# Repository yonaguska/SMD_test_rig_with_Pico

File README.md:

# SMD_test_rig_with_Pico
This is an automated test system for the SMD watchdog timers.

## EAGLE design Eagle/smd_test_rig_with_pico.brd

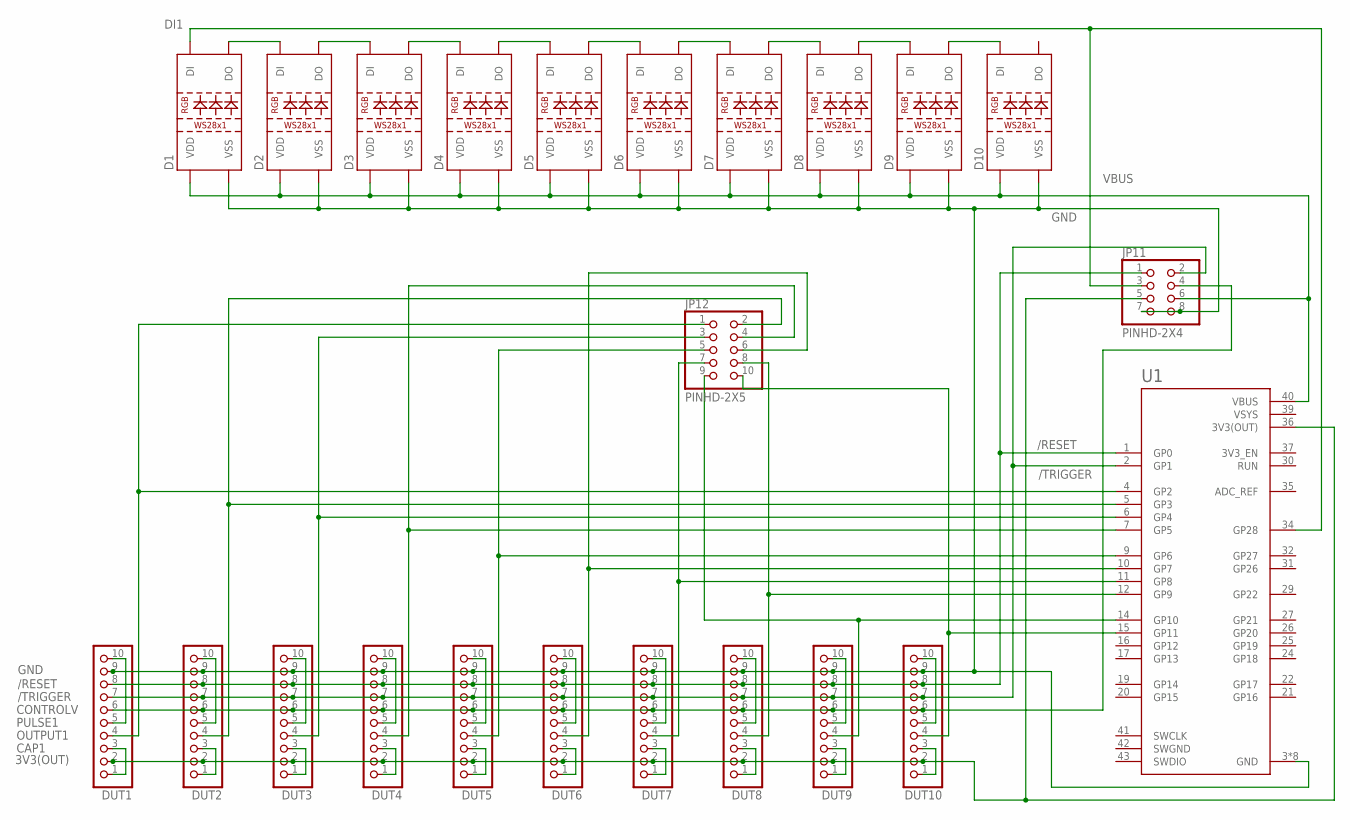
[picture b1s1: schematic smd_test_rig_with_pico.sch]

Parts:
D1, D2, D3, D4, D5, D6, D7, D8, D9, D10: WS2812B
DUT1, DUT2, DUT3, DUT4, DUT5, DUT6, DUT7, DUT8, DUT9, DUT10: PINHD-1X10; 1X10
JP11: PINHD-2X4; 2X04
JP12: PINHD-2X5; 2X05
U1: RASPBERRY_PICO; PICO-PKG-TH

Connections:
3V3(OUT): DUT1.2, DUT2.2, DUT3.2, DUT4.2, DUT5.2, DUT6.2, DUT7.2, DUT8.2, DUT9.2, DUT10.2, JP11.5, U1.36 (3V3(OUT))
/RESET: DUT1.8, DUT2.8, DUT3.8, DUT4.8, DUT5.8, DUT6.8, DUT7.8, DUT8.8, DUT9.8, DUT10.8, JP11.1, U1.1 (GP0)
/TRIGGER: DUT1.7, DUT2.7, DUT3.7, DUT4.7, DUT5.7, DUT6.7, DUT7.7, DUT8.7, DUT9.7, DUT10.7, JP11.2, U1.2 (GP1)
CAP1: DUT1.1, DUT1.3
CAP2: DUT2.1, DUT2.3
CAP3: DUT3.1, DUT3.3
CAP4: DUT4.1, DUT4.3
CAP5: DUT5.1, DUT5.3
CAP6: DUT6.1, DUT6.3
CAP7: DUT7.1, DUT7.3
CAP8: DUT8.1, DUT8.3
CAP9: DUT9.1, DUT9.3
CAP10: DUT10.1, DUT10.3
CONTROLV: DUT1.6, DUT2.6, DUT3.6, DUT4.6, DUT5.6, DUT6.6, DUT7.6, DUT8.6, DUT9.6, DUT10.6, JP11.4
DI1: D1.4 (DI), JP11.3, U1.34 (GP28)
GND: D1.3 (VSS), D2.3 (VSS), D3.3 (VSS), D4.3 (VSS), D5.3 (VSS), D6.3 (VSS), D7.3 (VSS), D8.3 (VSS), D9.3 (VSS), D10.3 (VSS), DUT1.9, DUT2.9, DUT3.9, DUT4.9, DUT5.9, DUT6.9, DUT7.9, DUT8.9, DUT9.9, DUT10.9, JP11.7, JP11.8, U1.3 (GND), U1.8 (GND), U1.13 (GND), U1.18 (GND), U1.23 (GND), U1.28 (GND), U1.33 (GND), U1.38 (GND)
unnamed: D1.2 (DO), D2.4 (DI)
unnamed: D2.2 (DO), D3.4 (DI)
unnamed: D3.2 (DO), D4.4 (DI)
unnamed: D4.2 (DO), D5.4 (DI)
unnamed: D5.2 (DO), D6.4 (DI)
unnamed: D6.2 (DO), D7.4 (DI)
unnamed: D7.2 (DO), D8.4 (DI)
unnamed: D8.2 (DO), D9.4 (DI)
unnamed: D9.2 (DO), D10.4 (DI)
OUTPUT1: DUT1.4, JP12.1, U1.4 (GP2)
OUTPUT2: DUT2.4, JP12.2, U1.5 (GP3)
OUTPUT3: DUT3.4, JP12.3, U1.6 (GP4)
OUTPUT4: DUT4.4, JP12.4, U1.7 (GP5)
OUTPUT5: DUT5.4, JP12.5, U1.9 (GP6)
OUTPUT6: DUT6.4, JP12.6, U1.10 (GP7)
OUTPUT7: DUT7.4, JP12.7, U1.11 (GP8)
OUTPUT8: DUT8.4, JP12.8, U1.12 (GP9)
OUTPUT9: DUT9.4, JP12.9, U1.14 (GP10)
OUTPUT10: DUT10.4, JP12.10, U1.15 (GP11)
PULSE1: DUT1.5, DUT1.10
PULSE2: DUT2.5, DUT2.10
PULSE3: DUT3.5, DUT3.10
PULSE4: DUT4.5, DUT4.10
PULSE5: DUT5.5, DUT5.10
PULSE6: DUT6.5, DUT6.10
PULSE7: DUT7.5, DUT7.10
PULSE8: DUT8.5, DUT8.10
PULSE9: DUT9.5, DUT9.10
PULSE10: DUT10.5, DUT10.10
SWGND: U1.42 (SWGND)
VBUS: D1.1 (VDD), D2.1 (VDD), D3.1 (VDD), D4.1 (VDD), D5.1 (VDD), D6.1 (VDD), D7.1 (VDD), D8.1 (VDD), D9.1 (VDD), D10.1 (VDD), JP11.6, U1.40 (VBUS)
VSYS: U1.39 (VSYS)

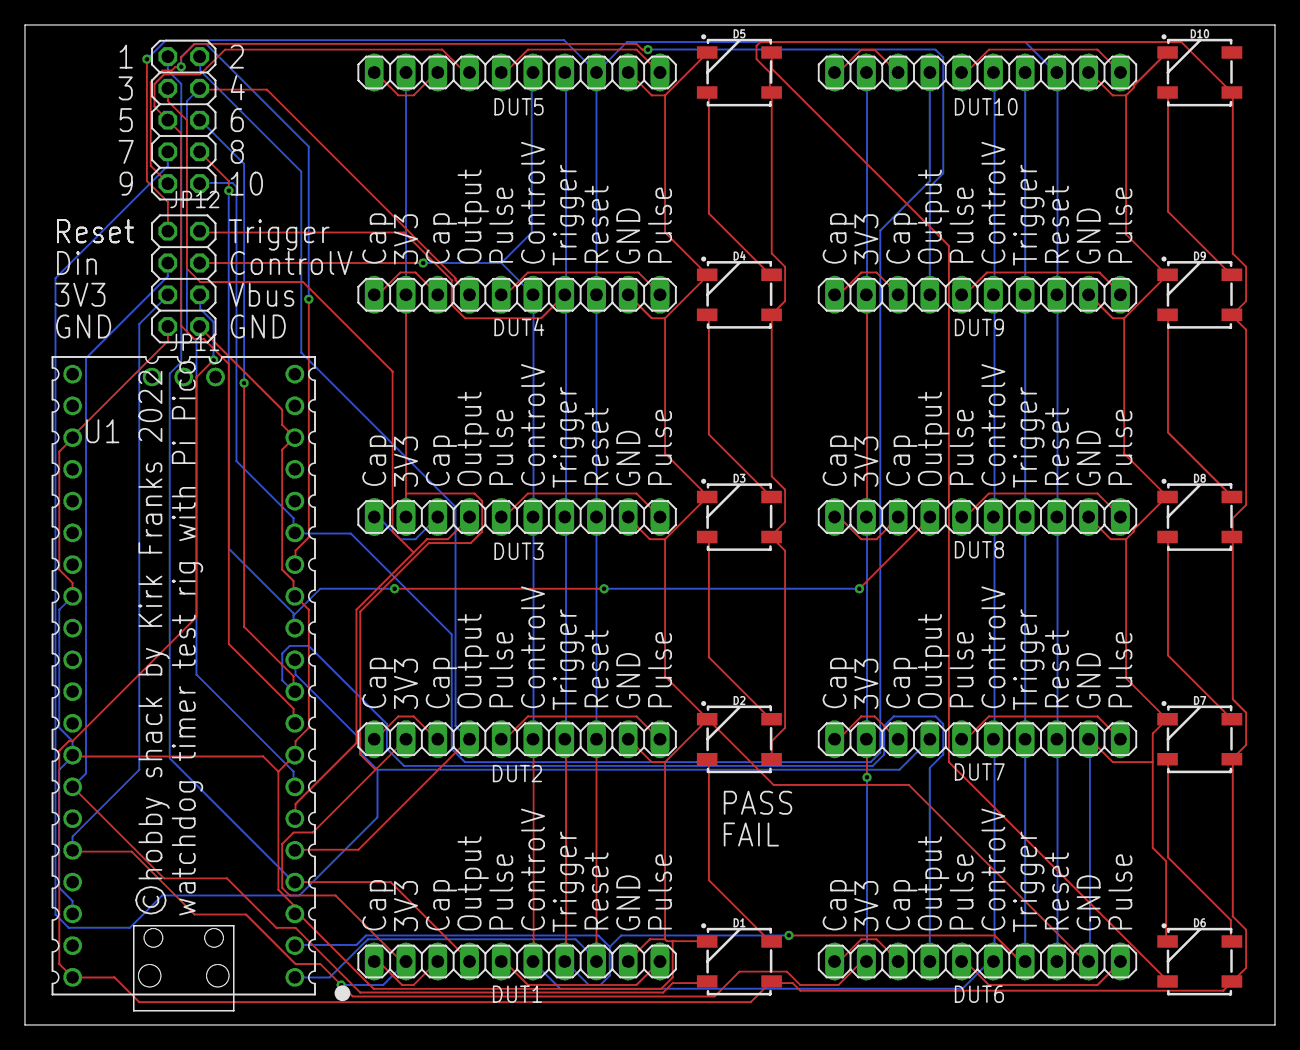
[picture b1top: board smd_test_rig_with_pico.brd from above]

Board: 2 copper layers, 100.0 x 80.0 mm, 23 parts (0 on the bottom side), 46 nets.

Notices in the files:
Eagle/smd_test_rig_with_pico.brd:
©hobby shack by Kirk Franks 2022
parts and their libraries:
SparkFun-LED: Licensing: Creative Commons ShareAlike 4.0 International - https://creativecommons.org/licenses/by-sa/4.0
